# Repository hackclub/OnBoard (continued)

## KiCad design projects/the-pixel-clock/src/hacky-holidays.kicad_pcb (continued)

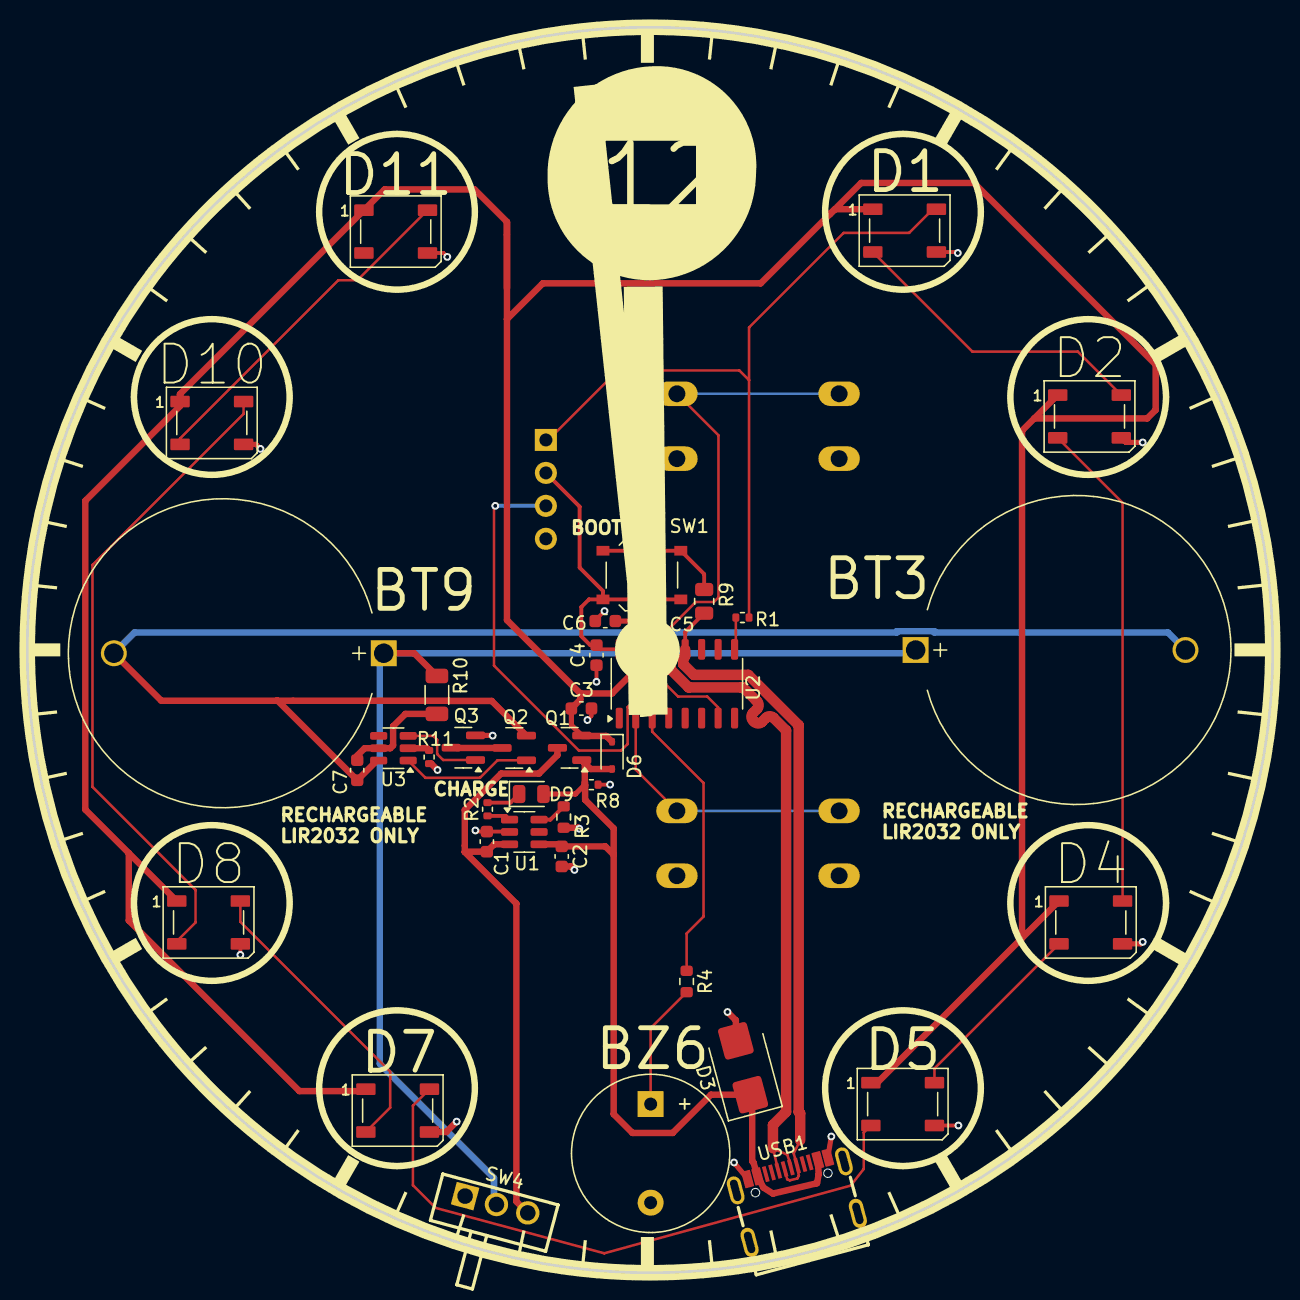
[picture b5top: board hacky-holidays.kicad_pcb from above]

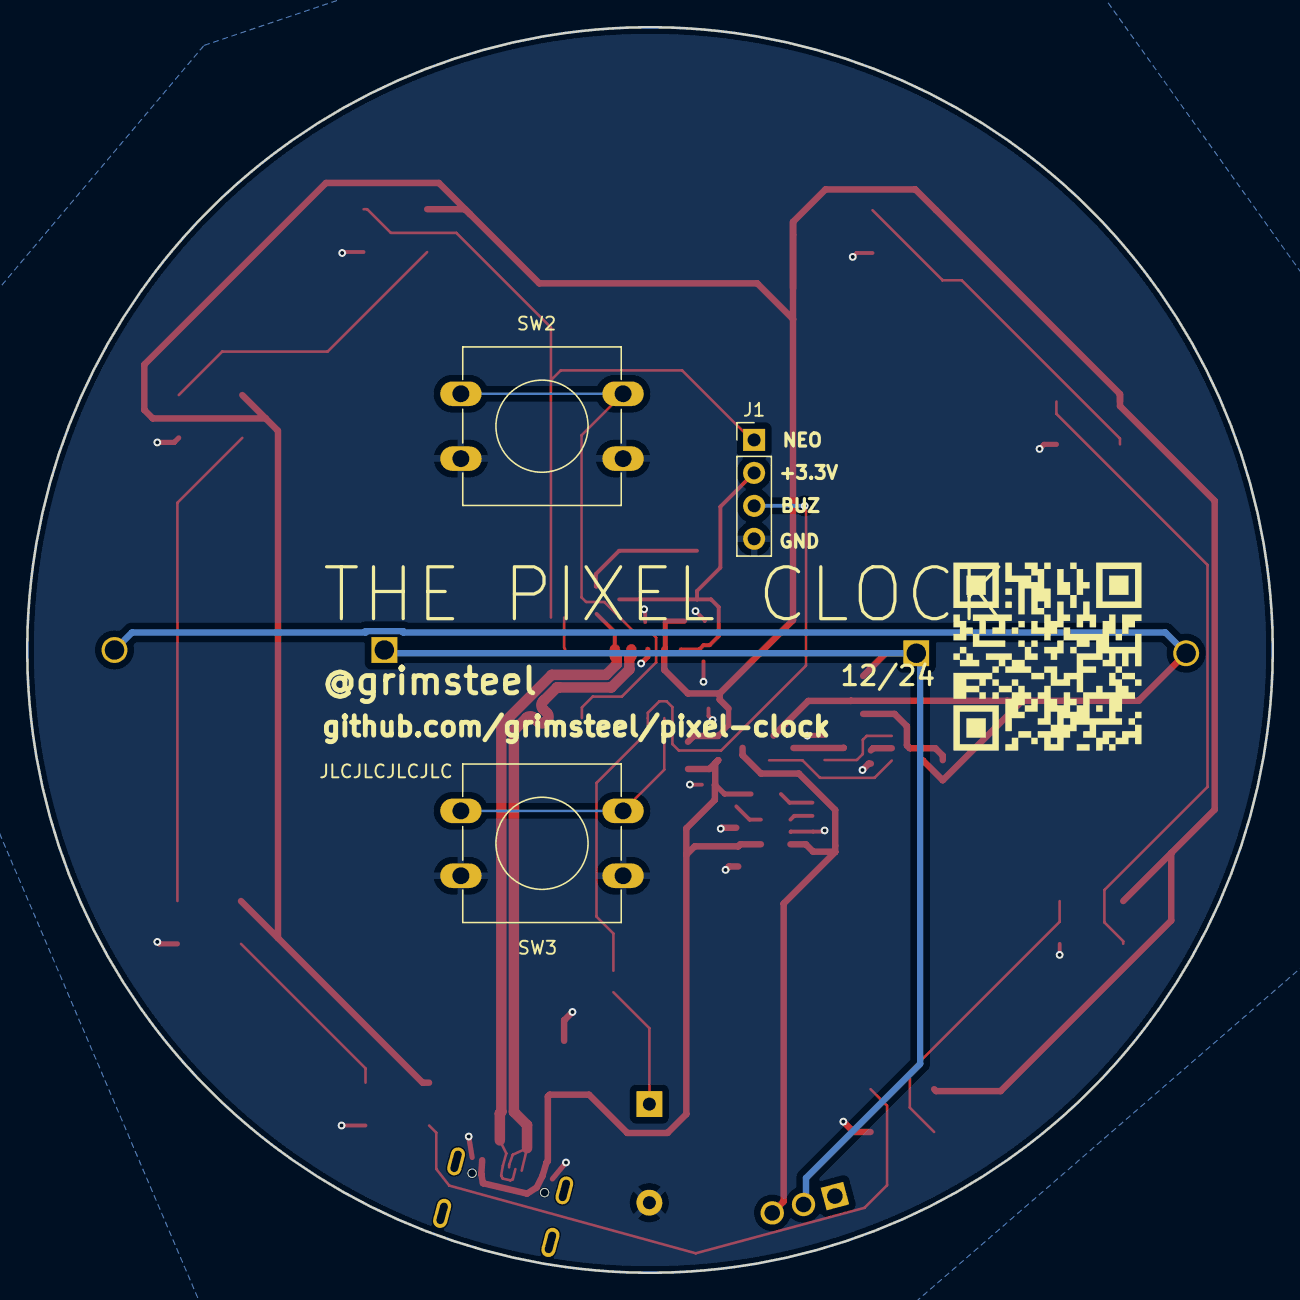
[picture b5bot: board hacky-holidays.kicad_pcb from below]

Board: 2 copper layers, 96.0 x 96.0 mm, 42 parts (4 on the bottom side), 31 nets.

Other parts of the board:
QR*****: https://github.com/grimsteel/pixel-clock; qrcode

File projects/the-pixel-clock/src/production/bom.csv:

Designator,Footprint,Quantity,Value,LCSC Part #
"BT3, BT9",BatteryHolder_MYOUNG_BS-07-A1BJ001_CR2032,2,Battery_Cell,C2979167
"C1, C6",0603,2,10 uF,C19702
"C2, C4, C5, C7",0603,4,100 nF,C14663
C3,0603,1,1 uF,C15849
"D1, D10, D11, D2, D4, D5, D7, D8",LED-SMD_4P-L1.6-W1.5_XL-1615RGBC-WS2812B,8,WS2812B,C5349954
D3,D_SMB,1,P6SMB6.8CA,C78395
D6,D_SOD-323,1,1N5819WS,C191023
D9,0805,1,LED,C84256
Q1,SOT-23,1,AO3401A,C15127
"Q2, Q3",SOT-23,2,AO3400A,C20917
R1,0402,1,330,C25104
R10,1206,1,100,C17901
"R11, R2",0402,2,1K,C11702
R3,0603,1,27K,C22967
R4,0603,1,220,C22962
"R5, R6",0603,2,5.1K,C23186
R8,0402,1,100K,C25741
R9,0805,1,10K,C17414
SW1,SW_Push_1P1T_XKB_TS-1187A,1,SW_Push,C318884
U1,SOT-23-6,1,TP4057,C12044
U2,STC_SOP-16_3.9x9.9mm_P1.27mm,1,CH552G,C111292
U3,SOT-23-6,1,DW01A,C18164398
USB1,USB-C_UC09-0B16F00P11,1,UC09-0B16F00P11,C36936538

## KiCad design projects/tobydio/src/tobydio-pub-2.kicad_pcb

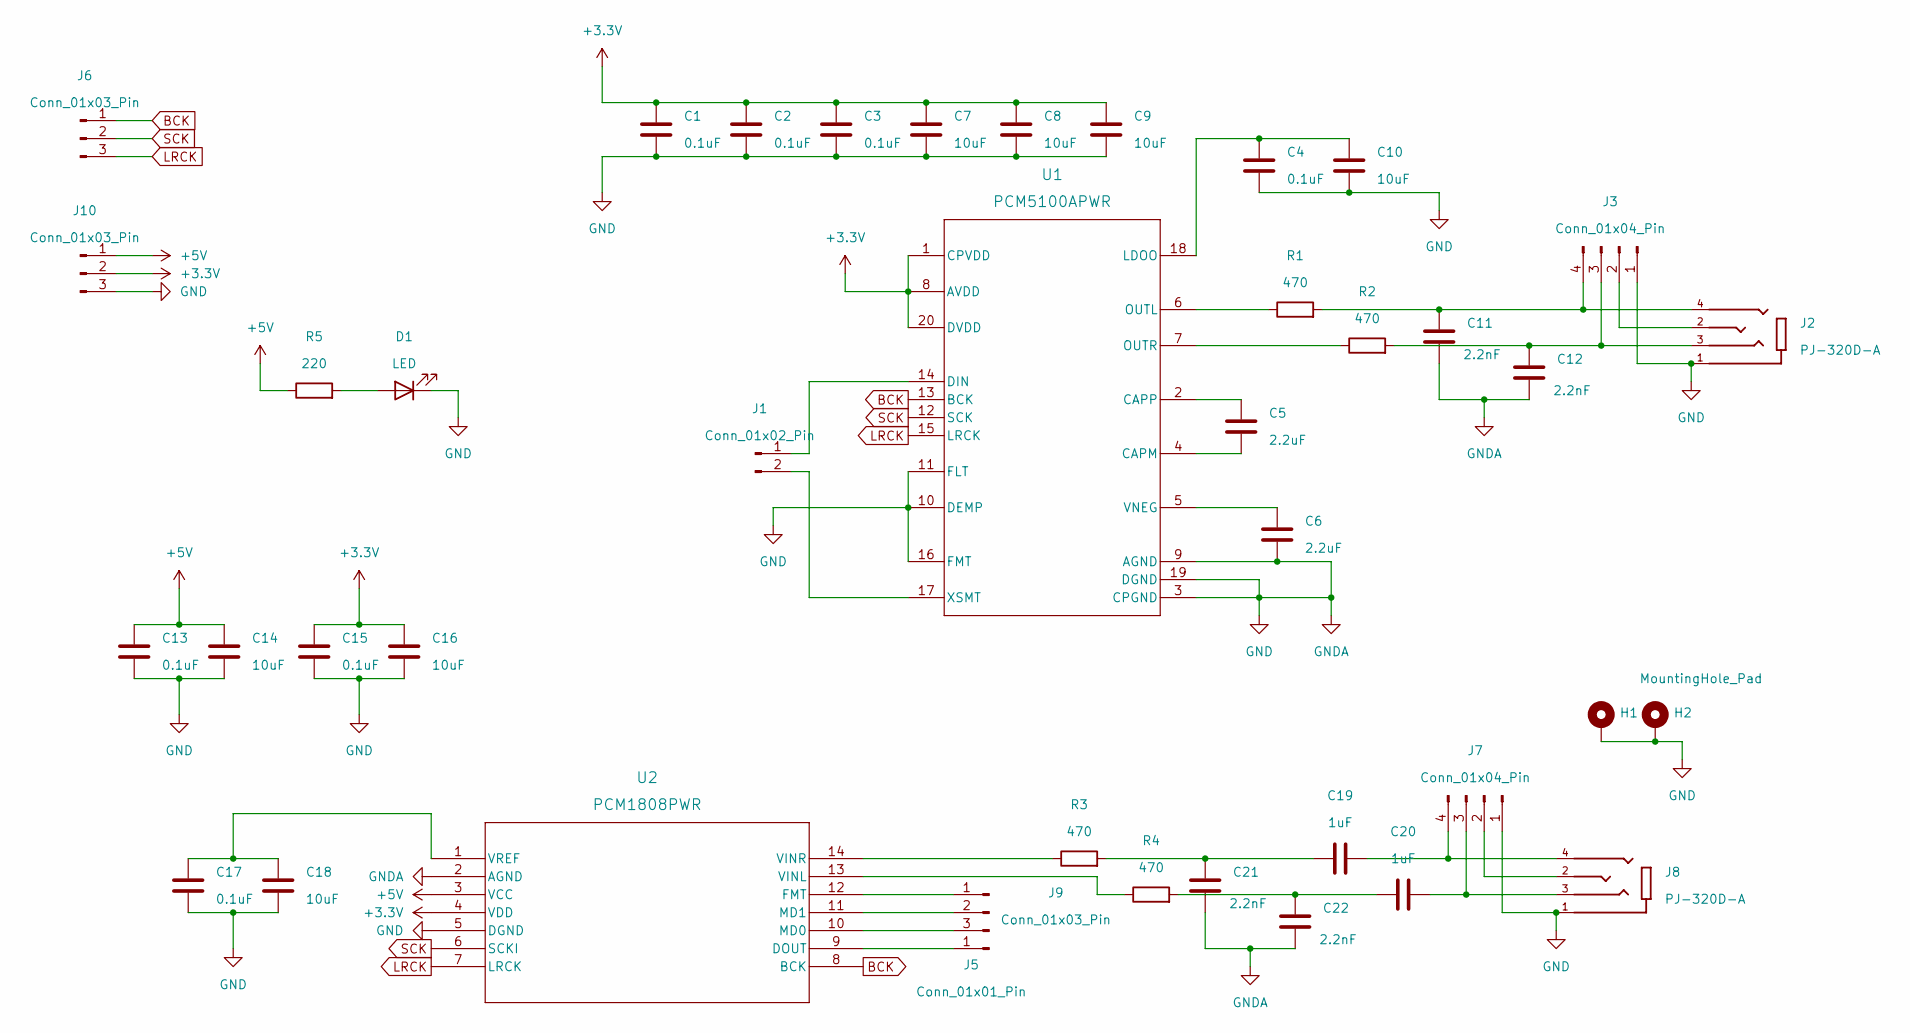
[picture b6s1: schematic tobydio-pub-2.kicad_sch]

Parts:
C1, C2, C3, C4, C13, C15, C17: 0.1uF; C_0402_1005Metric_Pad0.74x0.62mm_HandSolder; LCSC Part # C1525
C5, C6: 2.2uF; C_0603_1608Metric_Pad1.08x0.95mm_HandSolder; LCSC Part # C23630
C7, C8, C9, C10, C16: 10uF; C_0402_1005Metric_Pad0.74x0.62mm_HandSolder; LCSC Part # C15525
C11, C12, C21, C22: 2.2nF; C_0805_2012Metric_Pad1.18x1.45mm_HandSolder; LCSC Part # C28260
C14, C18: 10uF; C_0603_1608Metric_Pad1.08x0.95mm_HandSolder; LCSC Part # C19702
C19, C20: 1uF; C_0805_2012Metric_Pad1.18x1.45mm_HandSolder; LCSC Part # C28323
D1: LED; LED_0805_2012Metric_Pad1.15x1.40mm_HandSolder; LCSC Part # C2297
H1, H2: MountingHole_Pad; MountingHole_4.3mm_M4_Pad_Via
J1: Conn_01x02_Pin; PinHeader_1x02_P2.54mm_Vertical
J2, J8: PJ-320D-A; HRO_PJ-320D-A; PARTREV B
J3, J7: Conn_01x04_Pin; PinHeader_1x04_P2.54mm_Vertical
J5: Conn_01x01_Pin; PinHeader_1x01_P2.54mm_Vertical
J6, J9, J10: Conn_01x03_Pin; PinHeader_1x03_P2.54mm_Vertical
R1, R2, R3, R4: 470; R_0402_1005Metric_Pad0.72x0.64mm_HandSolder; LCSC Part # C25117
R5: 220; R_0402_1005Metric_Pad0.72x0.64mm_HandSolder; LCSC Part # C25091
U1: PCM5100APWR; PW0020A
U2: PCM1808PWR; PW14

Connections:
+3.3V: C1.1, C2.1, C3.1, C7.1, C8.1, C9.1, C15.1, C16.1, J10.2, U1.1 (CPVDD), U1.8 (AVDD), U1.20 (DVDD), U2.4 (VDD)
+5V: C13.1, C14.1, J10.1, R5.1, U2.3 (VCC)
BCK: J6.1, U1.13 (BCK), U2.8 (BCK)
GND: C1.2, C2.2, C3.2, C4.2, C6.2, C7.2, C8.2, C9.2, C10.2, C11.2, C12.2, C13.2, C14.2, C15.2, C16.2, C17.2, C18.2, C21.2, C22.2, D1.1 (K), H1.1, H2.1, J2.1, J3.1, J7.1, J8.1, J10.3, U1.3 (CPGND), U1.9 (AGND), U1.10 (DEMP), U1.11 (FLT), U1.16 (FMT), U1.19 (DGND), U2.2 (AGND), U2.5 (DGND)
LRCK: J6.3, U1.15 (LRCK), U2.7 (LRCK)
unnamed: C19.1, C21.1, R3.2
unnamed: C20.1, C22.1, R4.2
unnamed: D1.2 (A), R5.2
unnamed: J1.1, U1.14 (DIN)
unnamed: J1.2, U1.17 (XSMT)
unnamed: J2.2, J3.2
unnamed: C12.1, J2.3, J3.3, R2.2
unnamed: C11.1, J2.4, J3.4, R1.2
unnamed: J5.1, U2.9 (DOUT)
unnamed: J7.2, J8.2
unnamed: C20.2, J7.3, J8.3
unnamed: C19.2, J7.4, J8.4
unnamed: J9.1, U2.12 (FMT)
unnamed: J9.2, U2.11 (MD1)
unnamed: J9.3, U2.10 (MD0)
unnamed: C5.2, U1.4 (CAPM)
unnamed: C5.1, U1.2 (CAPP)
unnamed: C4.1, C10.1, U1.18 (LDOO)
unnamed: R1.1, U1.6 (OUTL)
unnamed: R2.1, U1.7 (OUTR)
unnamed: C6.1, U1.5 (VNEG)
unnamed: R4.1, U2.13 (VINL)
unnamed: R3.1, U2.14 (VINR)
unnamed: C17.1, C18.1, U2.1 (VREF)
SCK: J6.2, U1.12 (SCK), U2.6 (SCKI)

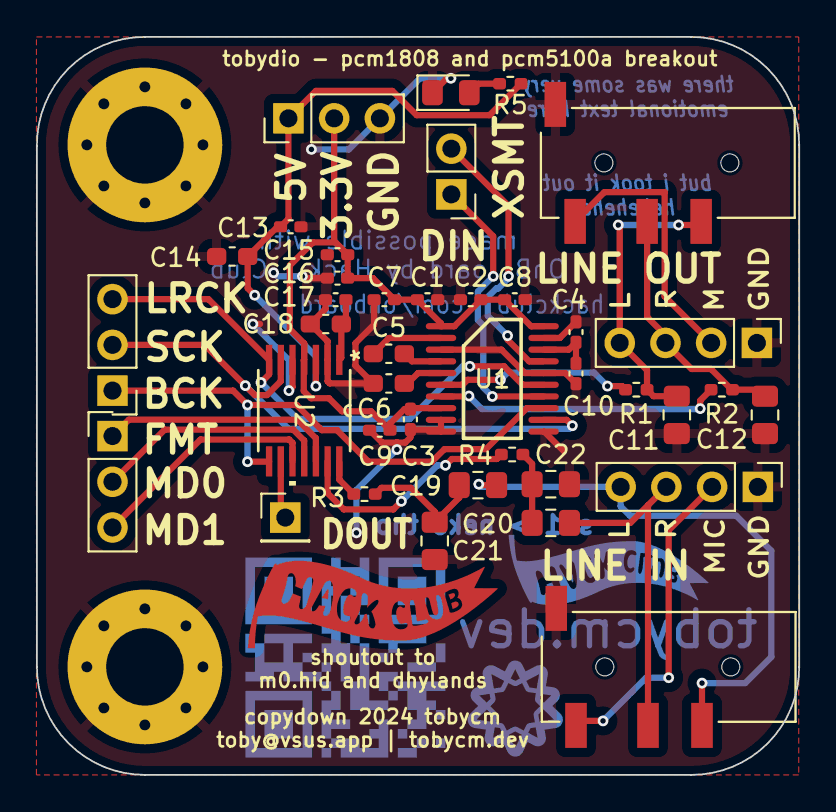
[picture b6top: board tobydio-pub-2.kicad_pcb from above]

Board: 2 copper layers, 42.4 x 41.0 mm, 41 parts (0 on the bottom side), 30 nets.
